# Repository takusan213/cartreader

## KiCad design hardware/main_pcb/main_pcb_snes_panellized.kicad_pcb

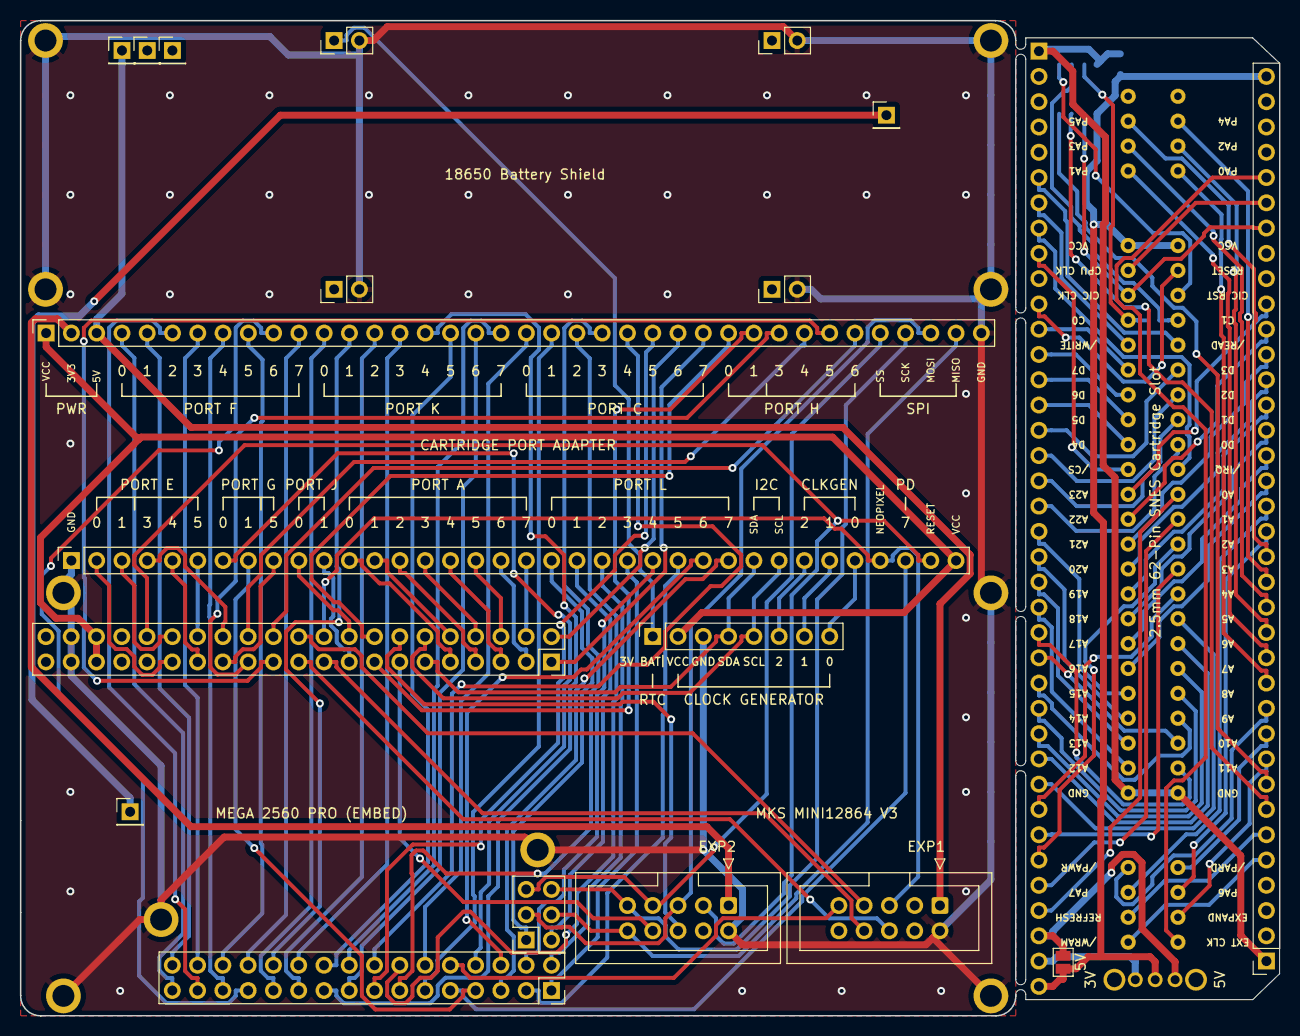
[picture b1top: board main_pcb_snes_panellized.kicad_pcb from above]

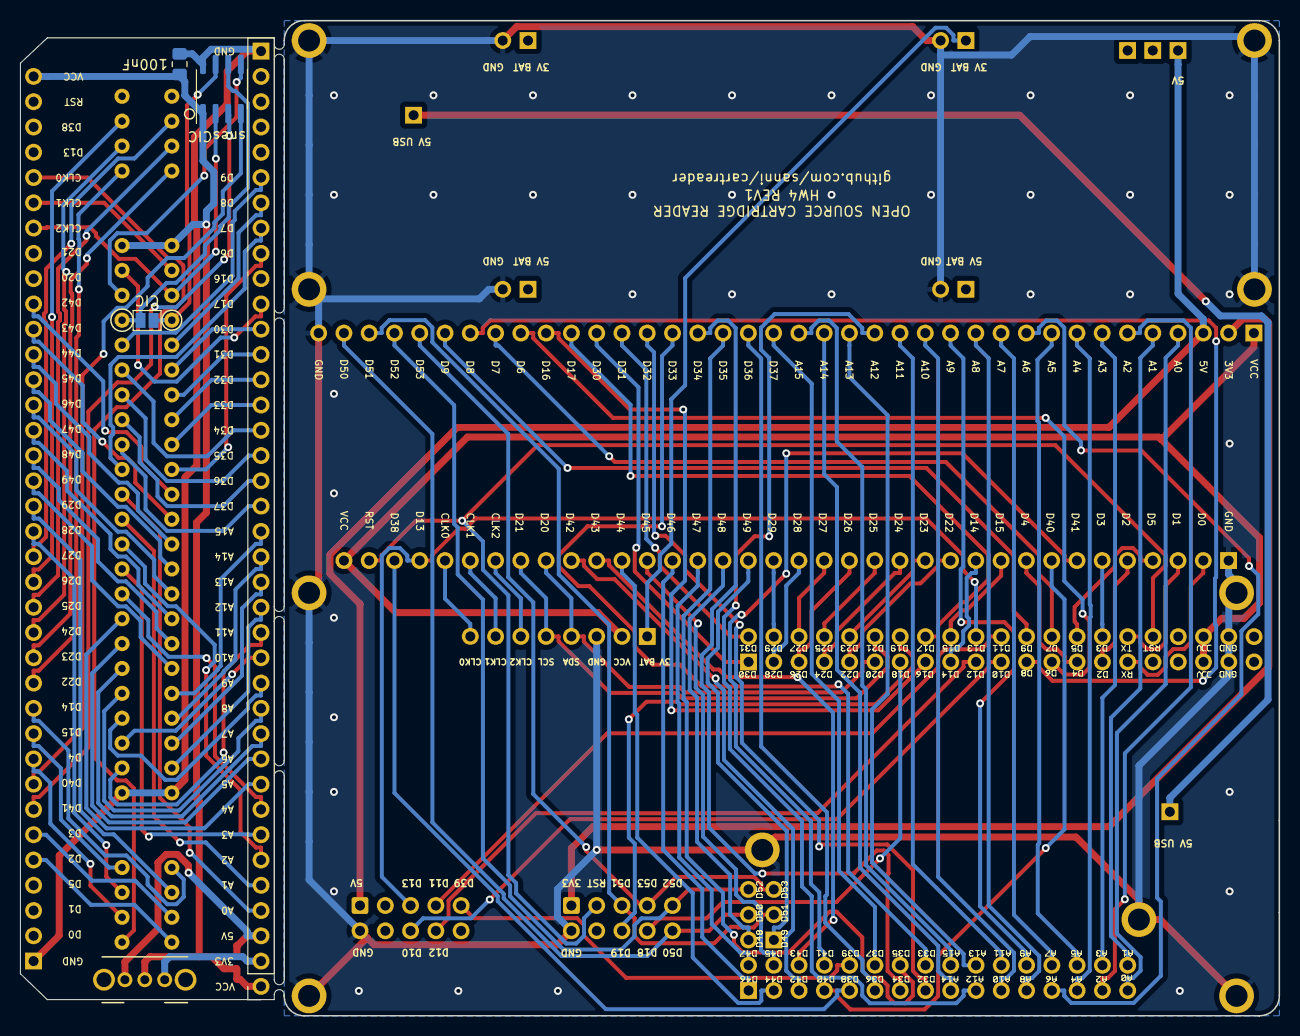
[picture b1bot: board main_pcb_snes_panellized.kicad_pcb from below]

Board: 2 copper layers, 126.5 x 100.0 mm, 35 parts (5 on the bottom side), 83 nets.

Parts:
C1: C_Small; C_0805_2012Metric_Pad1.18x1.45mm_HandSolder
J1: MEGA TOP; PinSocket_2x21_P2.54mm_Vertical
J1#2, J3#2: CART SLOT TOP ROW; PinSocket_1x38_P2.54mm_Vertical
J2, J4: CART SLOT BOTTOM ROW; PinSocket_1x36_P2.54mm_Vertical
J2#2: MEGA BOTTOM; PinSocket_2x16_P2.54mm_Vertical
J3: SNES_Slot; SNES Slot
J5: MEGA SIDE; PinSocket_2x03_P2.54mm_Vertical
J6, J16: 5V USB; PinHeader_1x01_P2.54mm_Vertical
J7, J9: 5V; PinHeader_1x01_P2.54mm_Vertical
J8: EXP2; IDC-Header_2x05_P2.54mm_Vertical
J10: N/A; PinHeader_1x01_P2.54mm_Vertical
J11, J12, J14, J15: Conn_01x02; PinHeader_1x02_P2.54mm_Vertical
J13: EXP1; IDC-Header_2x05_P2.54mm_Vertical
J17: Conn_01x08; PinSocket_1x08_P2.54mm_Vertical
JP1, JP2: SolderJumper_2_Open; SolderJumper-2_P1.3mm_Open_Pad1.0x1.5mm
M2_1, M2_2, M2_3, M2_4, M2_5, M2_6, M2_7, M2_8, M2_9, M2_10: Screw_Terminal_01x01; MountingHole_2.2mm_M2_ISO7380_Pad
SW1: SW_SPDT; SW_CuK_OS102011MA1QN1_SPDT_Angled
U1: PIC12F629-IP; SOIC-8_3.9x4.9mm_P1.27mm

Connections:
+3V3: J1#2.2, J3#2.2, J8.1, SW1.3 (C)
+5V: J1#2.3, J3#2.3, J7.1, J13.1, JP2.2 (B), SW1.1 (A)
+BATT: J11.1, J17.1
A0: J1#2.4, J2#2.31, J3.17 (A0), J3#2.4
A1: J1#2.5, J2#2.32, J3.16 (A1), J3#2.5
A2: J1#2.6, J2#2.29, J3.15 (A2), J3#2.6
A3: J1#2.7, J2#2.30, J3.14 (A3), J3#2.7
A4: J1#2.8, J2#2.27, J3.13 (A4), J3#2.8
A5: J1#2.9, J2#2.28, J3.12 (A5), J3#2.9
A6: J1#2.10, J2#2.25, J3.11 (A6), J3#2.10
A7: J1#2.11, J2#2.26, J3.10 (A7), J3#2.11
A8: J1#2.12, J2#2.23, J3.9 (A8), J3#2.12
A9: J1#2.13, J2#2.24, J3.8 (A9), J3#2.13
A10: J1#2.14, J2#2.21, J3.7 (A10), J3#2.14
A11: J1#2.15, J2#2.22, J3.6 (A11), J3#2.15
A12: J1#2.16, J2#2.19, J3.37 (A12), J3#2.16
A13: J1#2.17, J2#2.20, J3.38 (A13), J3#2.17
A14: J1#2.18, J2#2.17, J3.39 (A14), J3#2.18
A15: J1#2.19, J2#2.18, J3.40 (A15), J3#2.19
CIC DATA 0: J3.55 (CIC_data_out_(p2)), JP1.1 (A), U1.7 (GP0)
CIC DATA 1: J3.24 (CIC_out_data_(p1)), JP1.2 (B), U1.6 (GP1)
CIC RESET: J3.25 (CIC_in_data_(p7)), U1.5 (GP2)
CLK0: J2.32, J3.1 (21.477MHz_Clock), J4.32, J17.8
CLK1: J2.31, J3.57 (CPU_Clock), J4.31, J17.7
CLK2: J2.30, J3.56 (CIC_clock_in_(p6)), J4.30, J17.6, U1.2 (GP5)
D0: J1.31, J4.2
D1: J1.32, J4.3
D2: J1.29, J2.5, J3.32 (/WRAM), J4.5
D3: J1.30, J2.6, J3.33 (Refresh), J4.6
D4: J1.27, J2.9, J3.2 (Expand), J4.9
D5: J1.28, J4.4
D6: J1.25, J1#2.30, J3.49 (/Cart), J3#2.30
D7: J1.26, J1#2.31, J3.18 (/IRQ), J3#2.31
D8: J1.23, J1#2.32, J3.54 (/WR), J3#2.32
D9: J1.24, J1#2.33, J3.23 (/RD), J3#2.33
D10: J1.21, J13.6
D11: J1.22, J13.7
D12: J1.19, J13.8
D13: J1.20, J4.33, J13.5
D14: J1.17, J2.11, J3.35 (/PAWR), J4.11
D15: J1.18, J2.10, J3.4 (/PARD), J4.10
D16: J1.15, J3#2.29
D17: J1.16, J1#2.28, J3.26 (/RESET), J3#2.28
D18: J1.13, J8.8
D19: J1.14, J8.6
D20: J1.11, J4.28, J17.4
D21: J1.12, J4.29, J17.5
D22: J1.9, J2.12, J3.28 (PA0), J4.12
D23: J1.10, J2.13, J3.59 (PA1), J4.13
D24: J1.7, J2.14, J3.29 (PA2), J4.14
D25: J1.8, J2.15, J3.60 (PA3), J4.15
D26: J1.5, J2.16, J3.30 (PA4), J4.16
D27: J1.6, J2.17, J3.61 (PA5), J4.17
D28: J1.3, J2.18, J3.3 (PA6), J4.18
D29: J1.4, J2.19, J3.34 (PA7), J4.19
D30: J1.1, J1#2.27, J3.53 (D7), J3#2.27
D31: J1.2, J1#2.26, J3.52 (D6), J3#2.26
D32: J1#2.25, J2#2.15, J3.51 (D5), J3#2.25
D33: J1#2.24, J2#2.16, J3.50 (D4), J3#2.24
D34: J1#2.23, J2#2.13, J3.22 (D3), J3#2.23
D35: J1#2.22, J2#2.14, J3.21 (D2), J3#2.22
D36: J1#2.21, J2#2.11, J3.20 (D1), J3#2.21
D37: J1#2.20, J2#2.12, J3.19 (D0), J3#2.20
D38: J2#2.9, J4.34
D39: J2#2.10, J13.9
D40: J2.8, J2#2.7, J4.8, U1.4 (GP3)
D41: J2.7, J2#2.8, J4.7, U1.3 (GP4)
D42: J2.27, J2#2.5, J3.48 (BA7), J4.27
D43: J2.26, J2#2.6, J3.47 (BA6), J4.26
D44: J2.25, J2#2.3, J3.46 (BA5), J4.25
D45: J2.24, J2#2.4, J3.45 (BA4), J4.24
D46: J2.23, J2#2.1, J3.44 (BA3), J4.23
D47: J2.22, J2#2.2, J3.43 (BA2), J4.22
D48: J2.21, J3.42 (BA1), J4.21, J5.2
D49: J2.20, J3.41 (BA0), J4.20, J5.1
D50: J3#2.37, J5.4, J8.10
D51: J3#2.36, J5.3, J8.5
D52: J3#2.35, J5.6, J8.9
D53: J3#2.34, J5.5, J8.7
GND: C1.2, J1.39, J1.40, J1#2.38, J2.1, J3.5 (GND), J3.36 (GND), J3#2.38, J4.1, J8.2, J11.2, J12.2, J13.2, J14.2, J15.2, J17.3, M2_1.1, M2_2.1, M2_3.1, M2_4.1, M2_5.1, M2_6.1, M2_7.1, M2_8.1, M2_9.1, M2_10.1, U1.8 (VSS)
RESET: J1.34, J4.35, J8.3
VBUS: J6.1, J16.1
VCC: C1.1, J1.37, J1.38, J1#2.1, J2.36, J3.27 (VCC), J3.58 (VCC), J3#2.1, J4.36, J17.2, JP2.1 (A), SW1.2 (B), U1.1 (VDD)

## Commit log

2021-12-25 [add] panellized the snes adaptor PCB to the main PCB.
